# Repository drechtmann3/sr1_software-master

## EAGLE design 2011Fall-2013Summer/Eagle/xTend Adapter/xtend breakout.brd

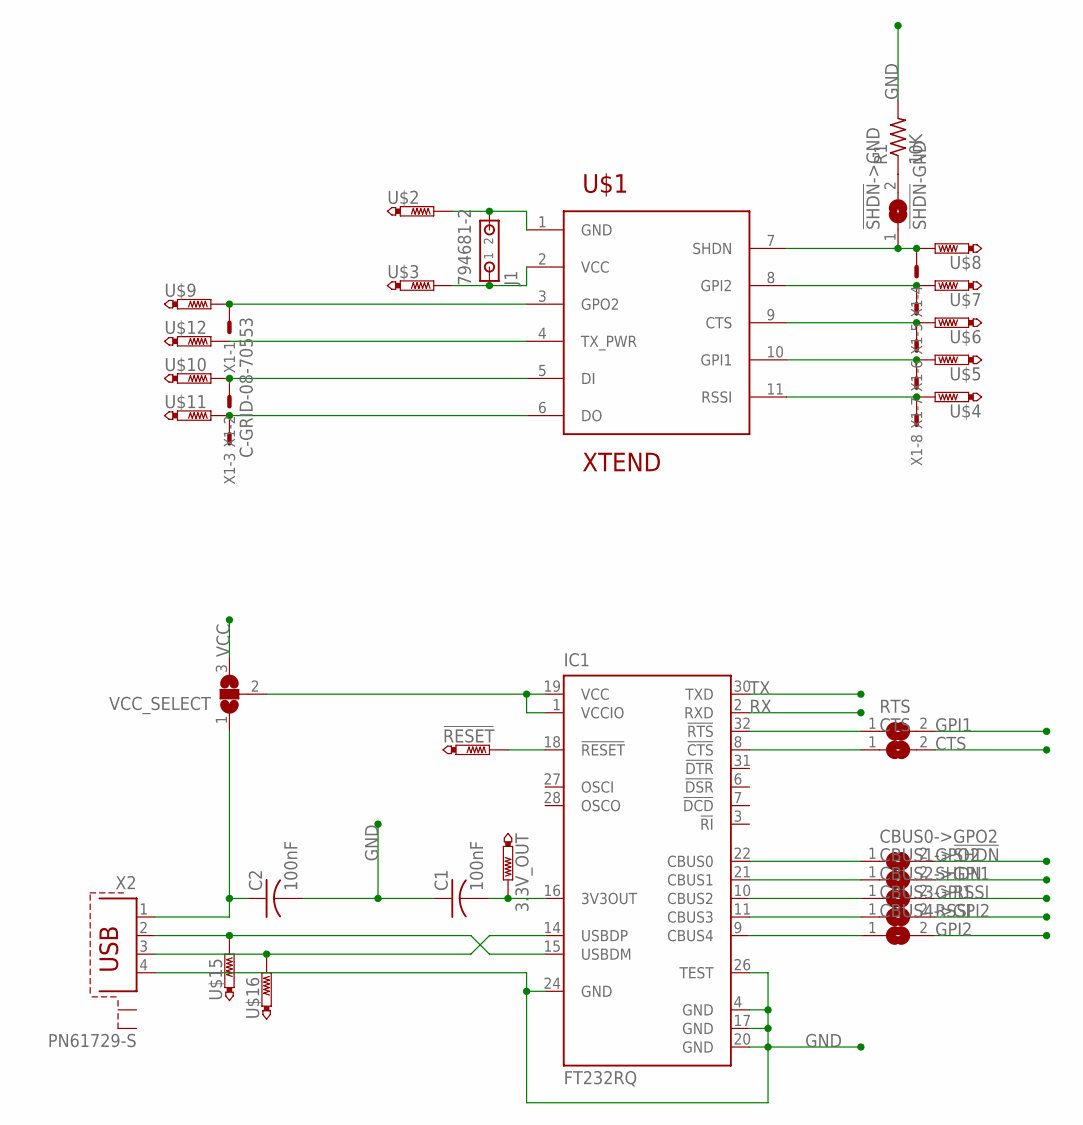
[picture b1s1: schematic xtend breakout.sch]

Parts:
3.3V_OUT: TESTPAD-20MIL; 20MIL
!RESET!: TESTPAD-20MIL; 20MIL
!SHDN!->GND: !SHDN!-GND; SJ
C1, C2: 100nF; C1206
CBUS0->GPO2, CBUS1->!SHDN!, CBUS2->GPI1, CBUS3->RSSI, CBUS4->GPI2: SJ
CTS: SJ
IC1: FT232RQ; QFN32
J1: 794681-2
R1: 10K; R1206
RTS: SJ
U$1: XTEND
U$2, U$3, U$4, U$5, U$6, U$7, U$8, U$9, U$10, U$11, U$12, U$15, U$16: TESTPAD-20MIL; 20MIL
VCC_SELECT: SJ2W; SJ_2
X1: C-GRID-08-70553; 70553-08
X2: PN61729-S

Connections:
CTS: CTS.2, U$1.9 (CTS), U$6.P$1, X1.6
GND: C1.1, C2.2, IC1.4 (GND), IC1.17 (GND), IC1.20 (GND), IC1.24 (GND), IC1.26 (TEST), J1.2, R1.2, U$1.1 (GND), U$2.P$1, X2.4
GPI1: CBUS2->GPI1.2, RTS.2, U$1.10 (GPI1), U$5.P$1, X1.7
GPI2: CBUS4->GPI2.2, U$1.8 (GPI2), U$7.P$1, X1.5
GPO2: CBUS0->GPO2.2, U$1.3 (GPO2), U$9.P$1, X1.1
unnamed: IC1.32 (!RTS), RTS.1
unnamed: CTS.1, IC1.8 (!CTS)
unnamed: !SHDN!->GND.2, R1.1
unnamed: CBUS0->GPO2.1, IC1.22 (CBUS0)
unnamed: CBUS1->!SHDN!.1, IC1.21 (CBUS1)
unnamed: CBUS2->GPI1.1, IC1.10 (CBUS2)
unnamed: CBUS3->RSSI.1, IC1.11 (CBUS3)
unnamed: CBUS4->GPI2.1, IC1.9 (CBUS4)
unnamed: IC1.1 (VCCIO), IC1.19 (VCC), VCC_SELECT.2
unnamed: 3.3V_OUT.P$1, C1.2, IC1.16 (3V3OUT)
unnamed: !RESET!.P$1, IC1.18 (!RESET)
RSSI: CBUS3->RSSI.2, U$1.11 (RSSI), U$4.P$1, X1.8
RX: IC1.2 (RXD), U$1.6 (DO), U$11.P$1, X1.3
SHDN: !SHDN!->GND.1, CBUS1->!SHDN!.2, U$1.7 (SHDN), U$8.P$1, X1.4
TX: IC1.30 (TXD), U$1.5 (DI), U$10.P$1, X1.2
TX_PWR: U$1.4 (TX_PWR), U$12.P$1
USBDM: IC1.15 (USBDM), U$15.P$1, X2.2
USBDP: IC1.14 (USBDP), U$16.P$1, X2.3
USB_VCC: C2.1, VCC_SELECT.1, X2.1
VCC: J1.1, U$1.2 (VCC), U$3.P$1, VCC_SELECT.3

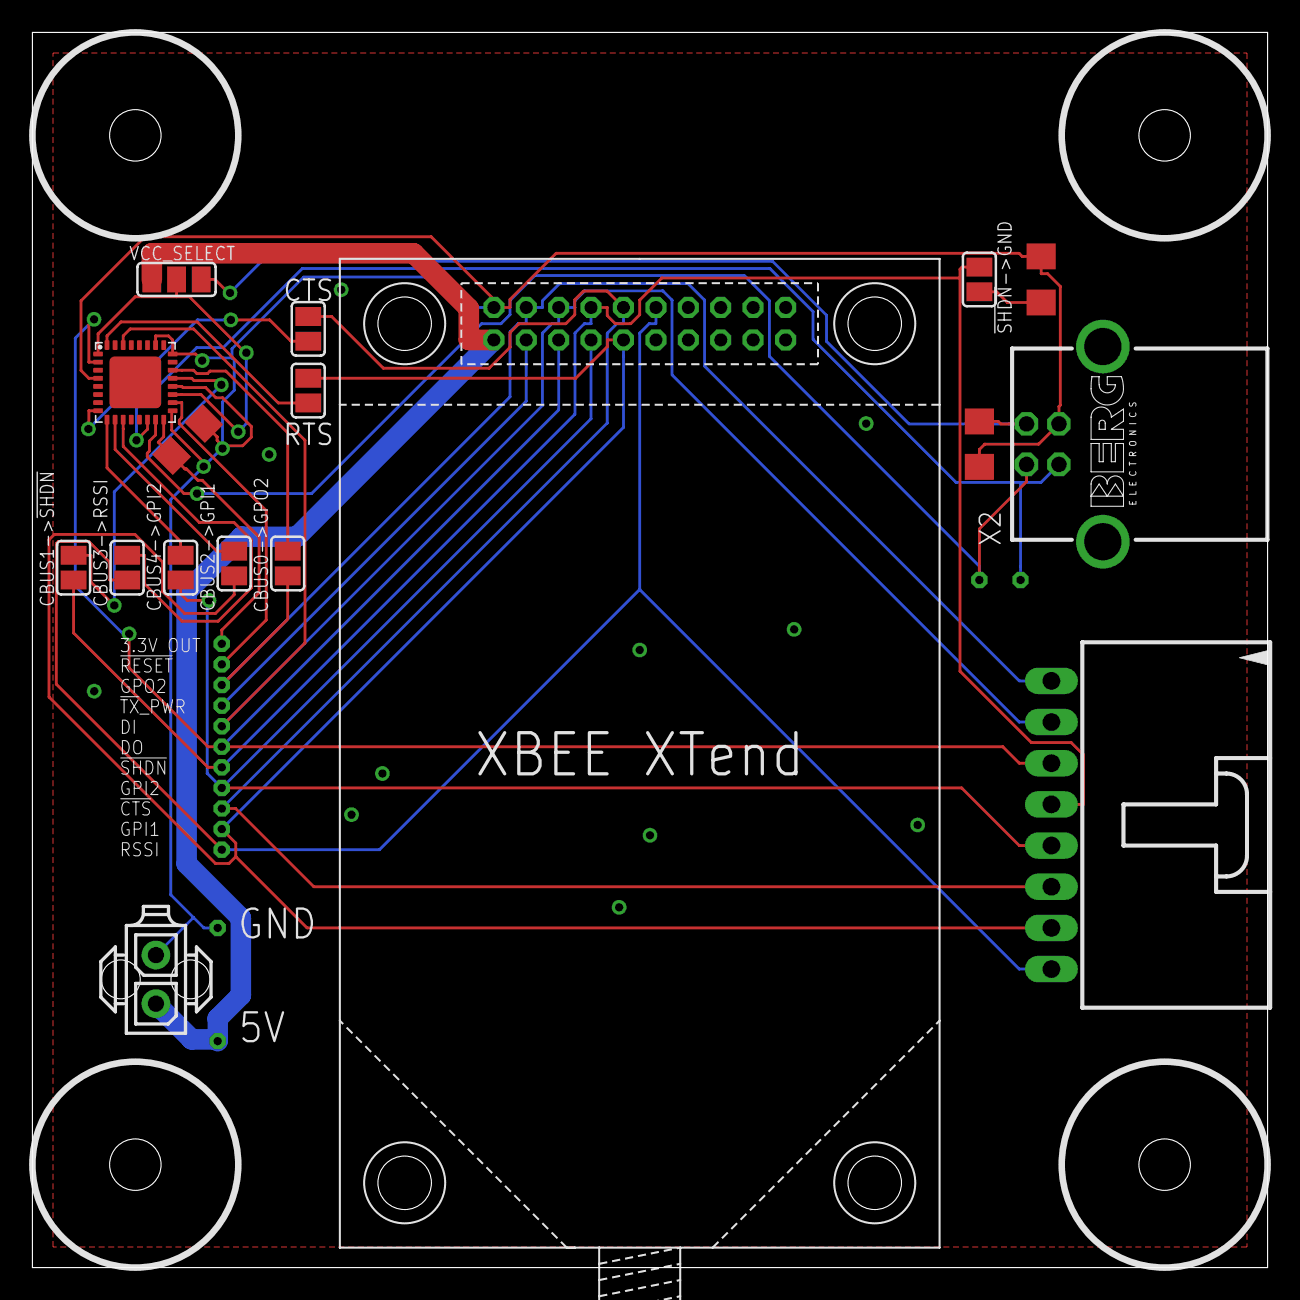
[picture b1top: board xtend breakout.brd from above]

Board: 2 copper layers, 76.2 x 76.2 mm, 32 parts (0 on the bottom side), 25 nets.
